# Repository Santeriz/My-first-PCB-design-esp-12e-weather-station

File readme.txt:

My first PCB design.

PCB gets power but the esp does not boot up, bad design.:)

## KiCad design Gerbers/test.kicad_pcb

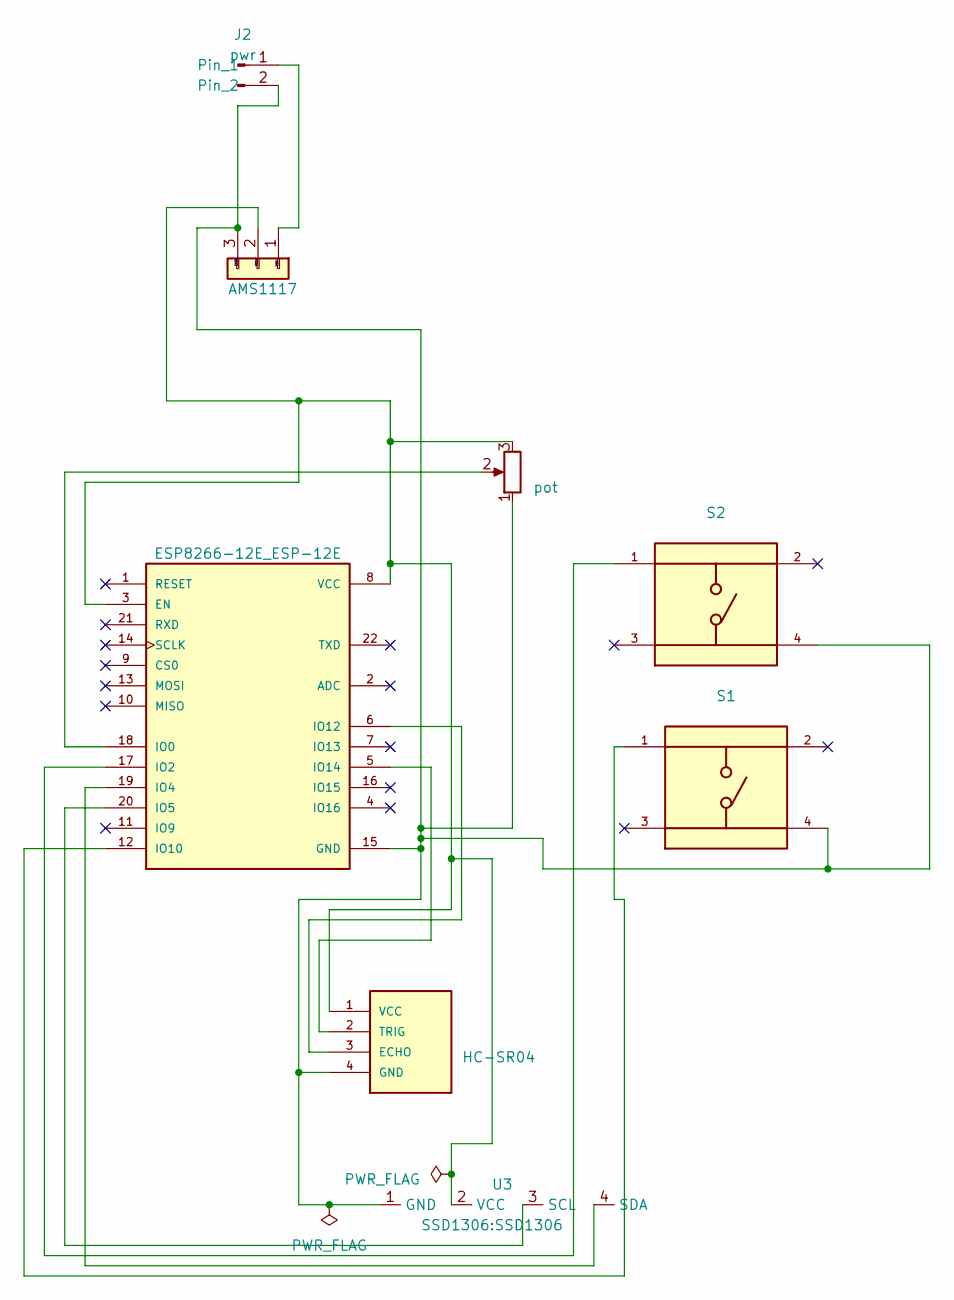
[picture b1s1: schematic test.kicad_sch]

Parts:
J1: AMS1117; ams_oma
J2: pwr; USB_pwr
RV1: pot; Potentiometer_Alps_RK09Y11_Single_Horizontal
S1, S2: TS02-66-43-BK-100-SCR-D; SW_TS02-66-43-BK-100-SCR-D; PARTREV 1.0
U1: HC-SR04; XCVR_HC-SR04
U2: ESP8266-12E_ESP-12E; XCVR_ESP8266-12E_ESP-12E
U3: SSD1306

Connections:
unnamed: J1.1, J2.1
unnamed: J1.2, RV1.3, U1.1 (VCC), U2.3 (EN), U2.8 (VCC), U3.2 (VCC)
unnamed: J1.3, J2.2, RV1.1, S1.4, S2.4, U1.4 (GND), U2.15 (GND), U3.1 (GND)
unnamed: U1.3 (ECHO), U2.6 (IO12)
unnamed: U1.2 (TRIG), U2.5 (IO14)
unnamed: RV1.2, U2.18 (IO0)
unnamed: S2.1, U2.17 (IO2)
unnamed: U2.19 (IO4), U3.4 (SDA)
unnamed: U2.20 (IO5), U3.3 (SCL)
unnamed: S1.1, U2.12 (IO10)

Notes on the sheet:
VIN
VOUT
GND

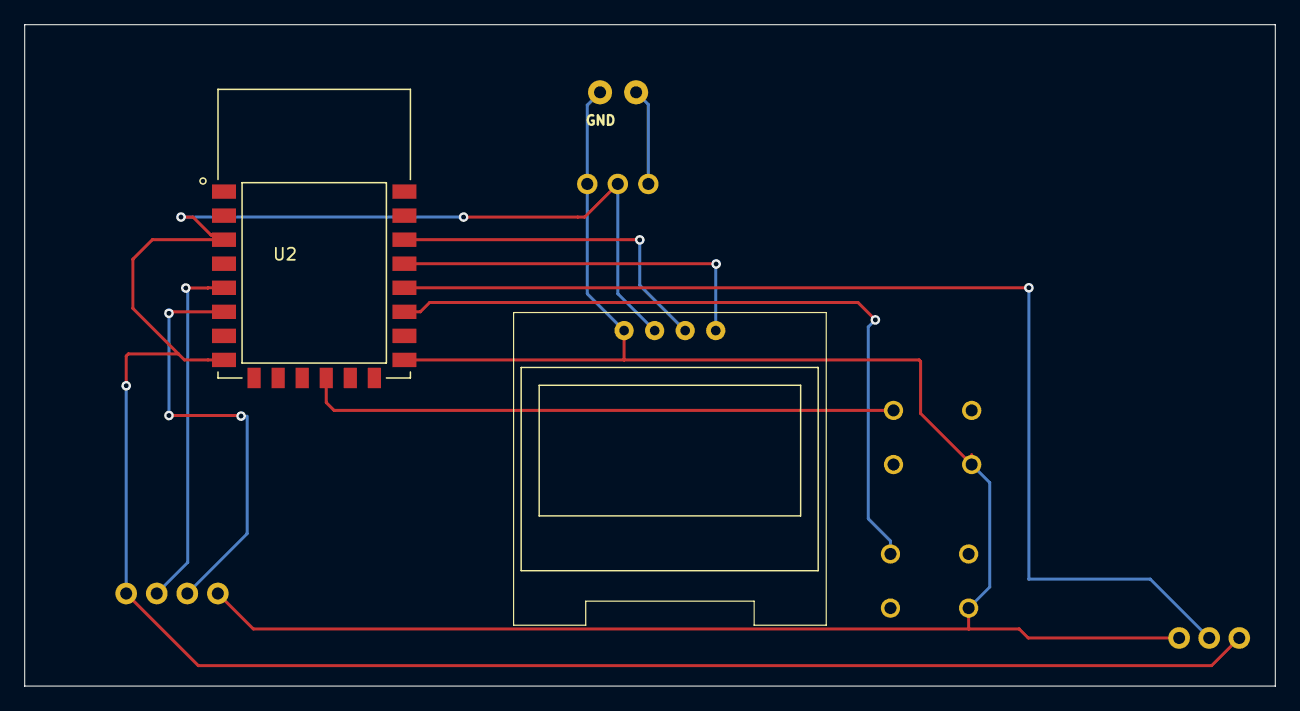
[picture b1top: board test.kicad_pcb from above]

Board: 4 copper layers, 104.0 x 55.0 mm, 8 parts (0 on the bottom side), 10 nets.
